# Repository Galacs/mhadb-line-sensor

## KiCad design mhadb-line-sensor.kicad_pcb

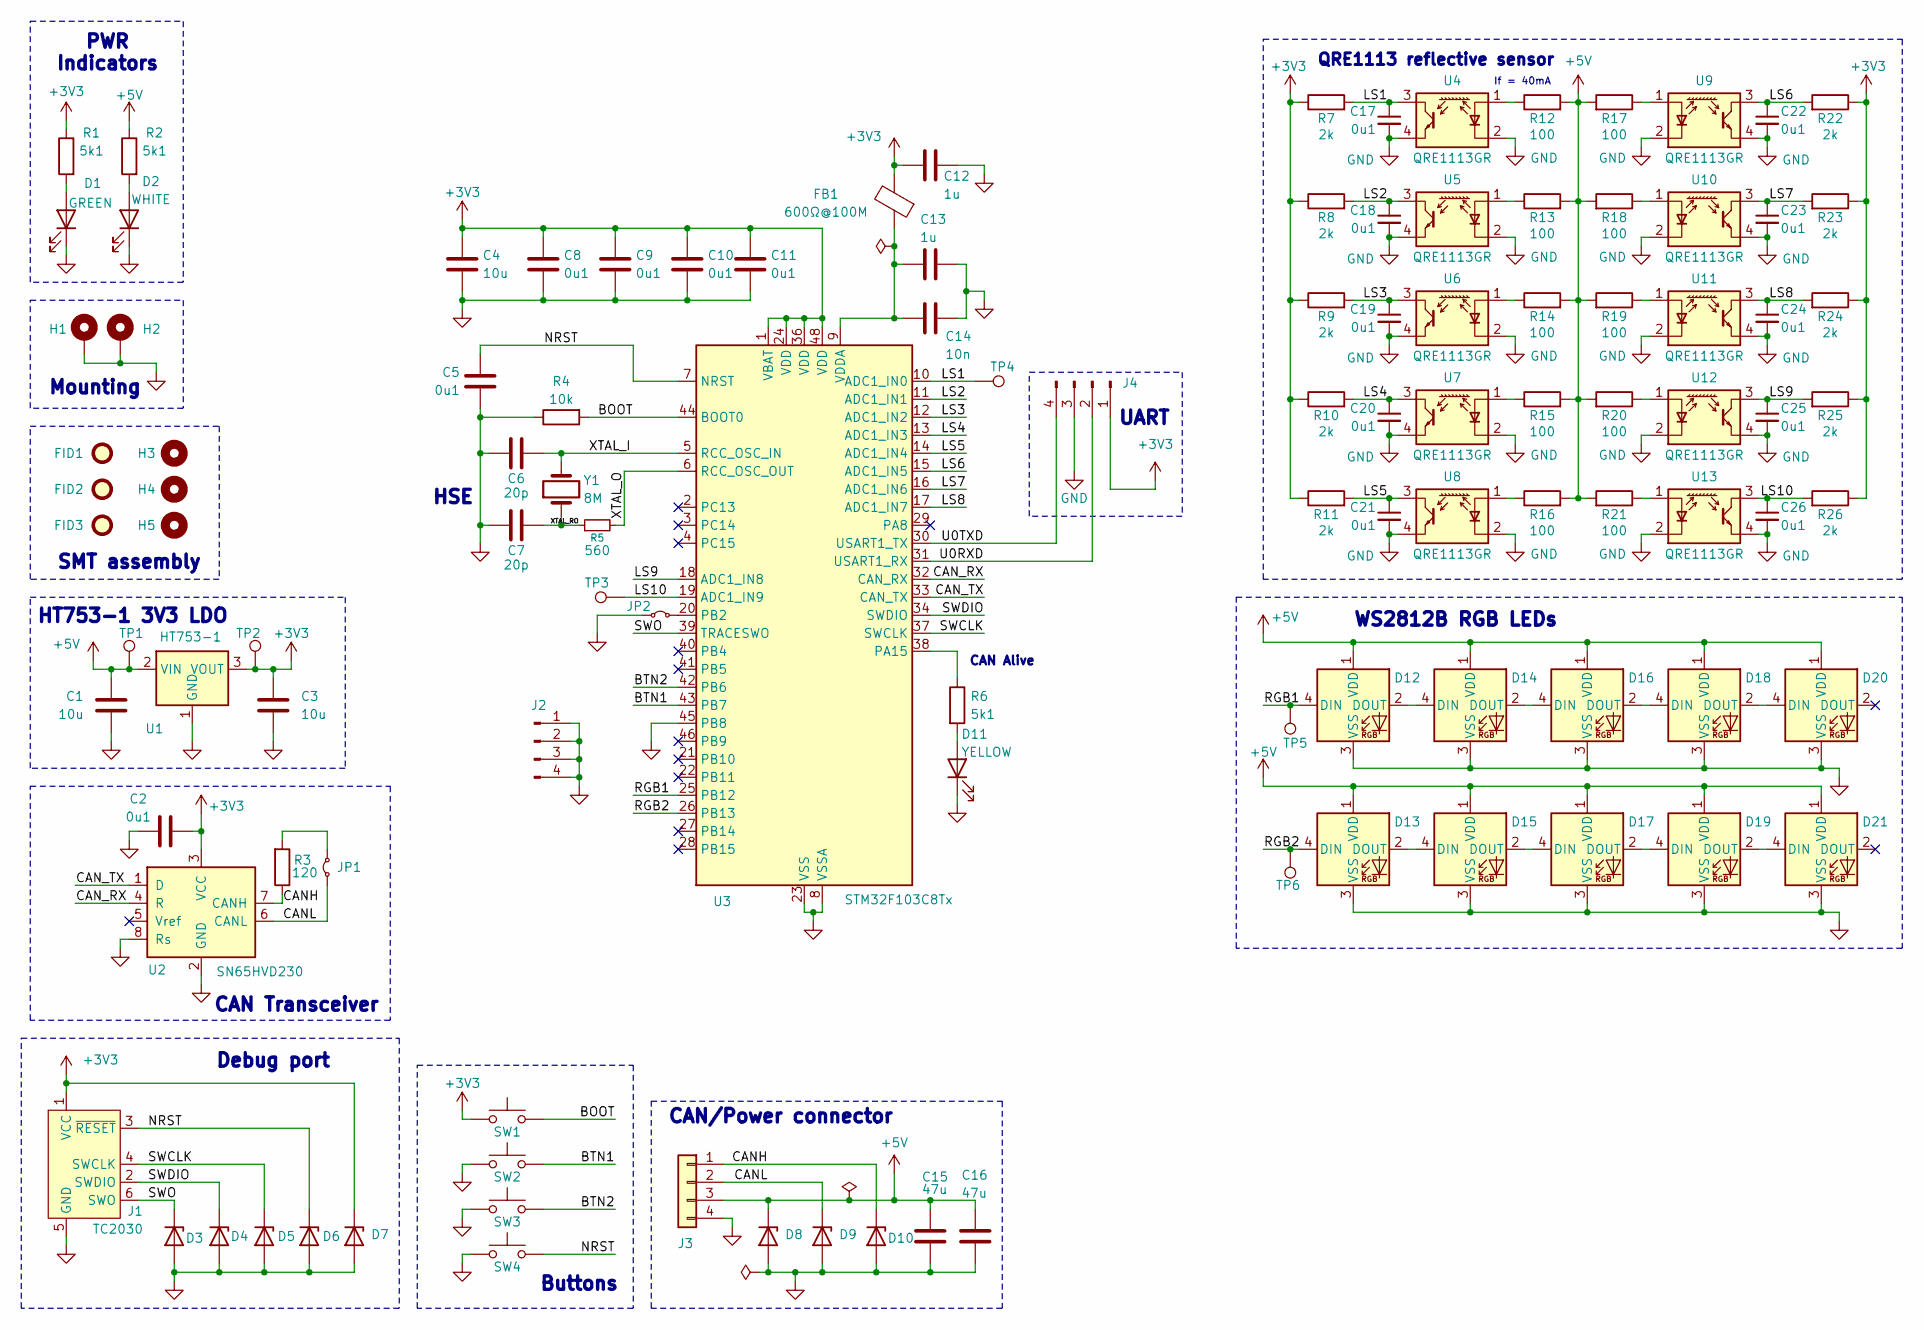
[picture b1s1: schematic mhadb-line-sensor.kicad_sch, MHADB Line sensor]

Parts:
C1, C3, C4: 10u; C_0805_2012Metric; Manufacturer Part Number GRM21BR61H106KE43L; JLCPCB Part # C440198
C2, C5, C8, C9, C10, C11, C17, C18, C19, C20, C21, C22, C23, C24, C25, C26: 0u1; C_0402_1005Metric; Manufacturer Part Number CL05B104KB54PNC; JLCPCB Part # C307331
C6, C7: 20p; C_0603_1608Metric; Manufacturer Part Number CL10C200JB8NNNC; JLCPCB Part # C1648
C12, C13: 1u; C_0402_1005Metric; Manufacturer Part Number CL05A105KA5NQNC; JLCPCB Part # C52923
C14: 10n; C_0402_1005Metric; Manufacturer Part Number CL05B103KB5NNNC; JLCPCB Part # C15195
C15, C16: 47u; C_1206_3216Metric; Manufacturer Part Number CL31A476MPHNNNE; JLCPCB Part # C96123
D1: GREEN; LED_0805_2012Metric; Manufacturer Part Number KT-0805G; JLCPCB Part # C2297
D2: WHITE; LED_0603_1608Metric; Manufacturer Part Number KT-0603W; JLCPCB Part # C2290
D3, D4, D5, D6, D7, D8, D9, D10: H5VU10U; Diode_DFN1006; Manufacturer Part Number H5VU10U; JLCPCB Part # C22395519
D11: YELLOW; LED_0805_2012Metric; Manufacturer Part Number KT-0805Y; JLCPCB Part # C2296
D12, D13, D14, D15, D16, D17, D18, D19, D20, D21: WS2812B; LED_WS2812B_PLCC4_5.0x5.0mm_P3.2mm; Manufacturer Part Number WS2812B-V5/W; JLCPCB Part # C2874885
FB1: 600Ω@100M; L_0805_2012Metric; Manufacturer Part Number MPZ2012S601ATD25; JLCPCB Part # C81034
FID1, FID2, FID3: Fiducial; Fiducial_1mm_Mask2mm
H1, H2: MountingHole_Pad; MountingHole_2.2mm_M2_Pad_Via
H3, H4, H5: MountingHole; ToolingHole_1.152mm
J1: TC2030; Tag-Connect_TC2030-IDC-NL_2x03_P1.27mm_Vertical
J2, J4: Conn_01x04_Pin; PinHeader_1x04_P2.54mm_Vertical
J3: Conn_01x04; JST_PH_S4B-PH-K_1x04_P2.00mm_Horizontal; Manufacturer Part Number S4B-PH-K-S(LF)(SN); JLCPCB Part # C157926
JP1: Jumper_2_Small_Bridged; SolderJumper-2_P1.3mm_Open_RoundedPad1.0x1.5mm
JP2: Jumper_2_Small_Bridged; SolderJumper-2_P1.3mm_Bridged_RoundedPad1.0x1.5mm
R1, R2, R6: 5k1; R_0402_1005Metric; Manufacturer Part Number 0402WGF5101TCE; JLCPCB Part # C25905
R3: 120; R_1206_3216Metric; Manufacturer Part Number 1206W4F1200T5E; JLCPCB Part # C17909
R4: 10k; R_0402_1005Metric; Manufacturer Part Number 0402WGF1002TCE; JLCPCB Part # C25744
R5: 560; R_0603_1608Metric; Manufacturer Part Number 0603WAF5600T5E; JLCPCB Part # C23204
R7, R8, R9, R10, R11, R22, R23, R24, R25, R26: 2k; R_0603_1608Metric; Manufacturer Part Number 0603WAF2201T5E; JLCPCB Part # C4190
R12, R13, R14, R15, R16, R17, R18, R19, R20, R21: 100; R_1206_3216Metric; Manufacturer Part Number 1206W4F1000T5E; JLCPCB Part # C17901
SW1, SW2, SW3, SW4: SW_Push; SW_SPST_TS-1088-xR020; Manufacturer Part Number TS-1088-AR02016; JLCPCB Part # C720477
TP1, TP2, TP3, TP4, TP5, TP6: TestPoint; TestPoint_Pad_D2.0mm
U1: HT753-1; SOT-89-3; Manufacturer Part Number HT7533-1; JLCPCB Part # C14289
U2: SN65HVD230; SOIC-8_3.9x4.9mm_P1.27mm; Manufacturer Part Number SN65HVD230DR; JLCPCB Part # C12084
U3: STM32F103C8Tx; LQFP-48_7x7mm_P0.5mm; Manufacturer Part Number STM32F103C8T6; JLCPCB Part # C8734
U4, U5, U6, U7, U8, U9, U10, U11, U12, U13: QRE1113GR; OnSemi_CASE100CY; Manufacturer Part Number QRE1113GR; JLCPCB Part # C232862
Y1: 8M; Crystal_SMD_5032-2Pin_5.0x3.2mm; Manufacturer Part Number X50328MSB2GI; JLCPCB Part # C115962

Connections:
+3V3: C2.1, C3.1, C4.1, C8.1, C9.1, C10.1, C11.1, C12.1, D7.1 (K), FB1.2, J1.1 (VCC), J4.1, R1.1, R7.1, R8.1, R9.1, R10.1, R11.1, R22.1, R23.1, R24.1, R25.1, R26.1, SW1.1, TP2.1, U1.3 (VOUT), U2.3 (VCC), U3.1 (VBAT), U3.24 (VDD), U3.36 (VDD), U3.48 (VDD)
+5V: C1.1, C15.1, C16.1, D8.1 (K), D12.1 (VDD), D13.1 (VDD), D14.1 (VDD), D15.1 (VDD), D16.1 (VDD), D17.1 (VDD), D18.1 (VDD), D19.1 (VDD), D20.1 (VDD), D21.1 (VDD), J3.3, R2.1, R12.2, R13.2, R14.2, R15.2, R16.2, R17.2, R18.2, R19.2, R20.2, R21.2, TP1.1, U1.2 (VIN)
/BOOT: R4.2, SW1.2, U3.44 (BOOT0)
/BTN1: SW2.2, U3.43 (PB7)
/BTN2: SW3.2, U3.42 (PB6)
/CANH: D10.1 (K), J3.1, R3.1, U2.7 (CANH)
/CANL: D9.1 (K), J3.2, JP1.1 (A), U2.6 (CANL)
/CAN_RX: U2.4 (R), U3.32 (CAN_RX)
/CAN_TX: U2.1 (D), U3.33 (CAN_TX)
/LS1: C17.1, R7.2, TP4.1, U3.10 (ADC1_IN0), U4.3
/LS2: C18.1, R8.2, U3.11 (ADC1_IN1), U5.3
/LS3: C19.1, R9.2, U3.12 (ADC1_IN2), U6.3
/LS4: C20.1, R10.2, U3.13 (ADC1_IN3), U7.3
/LS5: C21.1, R11.2, U3.14 (ADC1_IN4), U8.3
/LS6: C22.1, R22.2, U3.15 (ADC1_IN5), U9.3
/LS7: C23.1, R23.2, U3.16 (ADC1_IN6), U10.3
/LS8: C24.1, R24.2, U3.17 (ADC1_IN7), U11.3
/LS9: C25.1, R25.2, U3.18 (ADC1_IN8), U12.3
/LS10: C26.1, R26.2, TP3.1, U3.19 (ADC1_IN9), U13.3
/NRST: C5.1, D6.1 (K), J1.3 (~RESET), SW4.2, U3.7 (NRST)
/RGB1: D12.4 (DIN), TP5.1, U3.25 (PB12)
/RGB2: D13.4 (DIN), TP6.1, U3.26 (PB13)
/SWCLK: D5.1 (K), J1.4 (SWCLK), U3.37 (SWCLK)
/SWDIO: D4.1 (K), J1.2 (SWDIO), U3.34 (SWDIO)
/SWO: D3.1 (K), J1.6 (SWO), U3.39 (TRACESWO)
/U0RXD: J4.2, U3.31 (USART1_RX)
/U0TXD: J4.4, U3.30 (USART1_TX)
/XTAL_I: C6.1, U3.5 (RCC_OSC_IN), Y1.2
/XTAL_O: R5.2, U3.6 (RCC_OSC_OUT)
/XTAL_RO: C7.1, R5.1, Y1.1
GND: C1.2, C2.2, C3.2, C4.2, C5.2, C6.2, C7.2, C8.2, C9.2, C10.2, C11.2, C12.2, C13.2, C14.2, C15.2, C16.2, C17.2, C18.2, C19.2, C20.2, C21.2, C22.2, C23.2, C24.2, C25.2, C26.2, D1.1 (K), D2.1 (K), D3.2 (A), D4.2 (A), D5.2 (A), D6.2 (A), D7.2 (A), D8.2 (A), D9.2 (A), D10.2 (A), D11.1 (K), D12.3 (VSS), D13.3 (VSS), D14.3 (VSS), D15.3 (VSS), D16.3 (VSS), D17.3 (VSS), D18.3 (VSS), D19.3 (VSS), D20.3 (VSS), D21.3 (VSS), H1.1, H2.1, J1.5 (GND), J2.1, J2.2, J2.3, J2.4, J3.4, J4.3, JP2.1 (A), R4.1, SW2.1, SW3.1, SW4.1, U1.1 (GND), U2.2 (GND), U2.8 (Rs), U3.8 (VSSA), U3.23 (VSS), U3.35 (VSS), U3.45 (PB8), U3.47 (VSS), U4.2 (K), U4.4, U5.2 (K), U5.4, U6.2 (K), U6.4, U7.2 (K), U7.4, U8.2 (K), U8.4, U9.2 (K), U9.4, U10.2 (K), U10.4, U11.2 (K), U11.4, U12.2 (K), U12.4, U13.2 (K), U13.4
unnamed: D1.2 (A), R1.2
unnamed: D2.2 (A), R2.2
unnamed: D11.2 (A), R6.2
unnamed: D12.2 (DOUT), D14.4 (DIN)
unnamed: D13.2 (DOUT), D15.4 (DIN)
unnamed: D14.2 (DOUT), D16.4 (DIN)
unnamed: D15.2 (DOUT), D17.4 (DIN)
unnamed: D16.2 (DOUT), D18.4 (DIN)
unnamed: D17.2 (DOUT), D19.4 (DIN)
unnamed: D18.2 (DOUT), D20.4 (DIN)
unnamed: D19.2 (DOUT), D21.4 (DIN)
unnamed: JP1.2 (B), R3.2
unnamed: JP2.2 (B), U3.20 (PB2)
unnamed: R6.1, U3.38 (PA15)
unnamed: C13.1, C14.1, FB1.1, U3.9 (VDDA)
unnamed: R12.1, U4.1 (A)
unnamed: R13.1, U5.1 (A)
unnamed: R14.1, U6.1 (A)
unnamed: R15.1, U7.1 (A)
unnamed: R16.1, U8.1 (A)
unnamed: R17.1, U9.1 (A)
unnamed: R18.1, U10.1 (A)
unnamed: R19.1, U11.1 (A)
unnamed: R20.1, U12.1 (A)
unnamed: R21.1, U13.1 (A)

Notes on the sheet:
CAN Transceiver
WS2812B RGB LEDs
Buttons
CAN Alive
If = 40mA
UART
PWR Indicators
SMT assembly
QRE1113 reflective sensor
Mounting
HT753-1 3V3 LDO
Debug port
CAN/Power connector
HSE

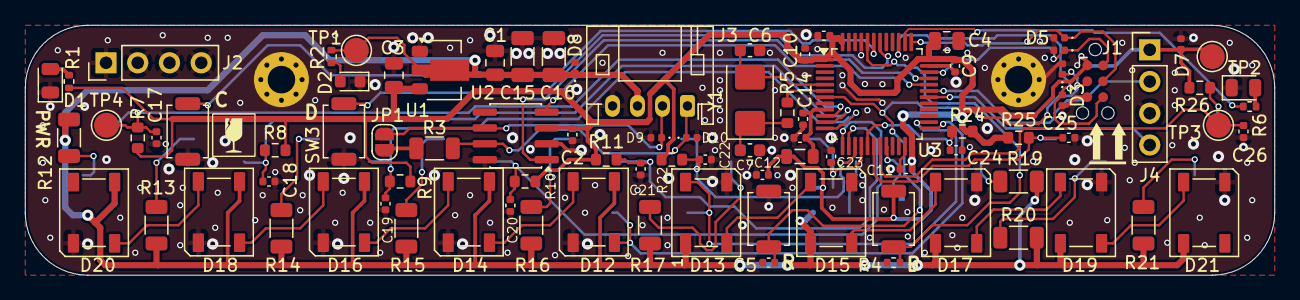
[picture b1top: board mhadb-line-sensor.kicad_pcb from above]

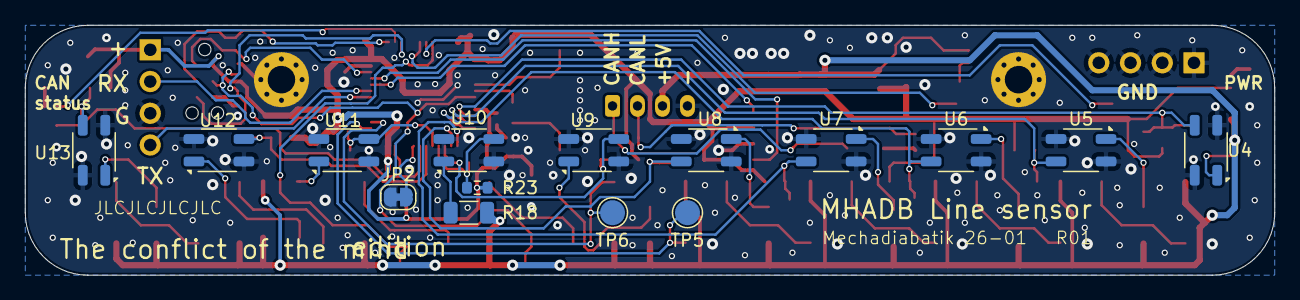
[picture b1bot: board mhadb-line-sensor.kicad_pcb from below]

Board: 2 copper layers, 100.0 x 20.0 mm, 106 parts (15 on the bottom side), 56 nets.

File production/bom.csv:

Designator,Footprint,Quantity,Value,LCSC Part #
"C1, C3, C4",0805,3,10u,C440198
"C10, C11, C17, C18, C19, C2, C20, C21, C22, C23, C24, C25, C26, C5, C8, C9",0402,16,0u1,C307331
"C12, C13",0402,2,1u,C52923
C14,0402,1,10n,C15195
"C15, C16",1206,2,47u,C96123
"C6, C7",0603,2,20p,C1648
D1,0805,1,GREEN,C2297
"D10, D3, D4, D5, D6, D7, D8, D9",Diode_DFN1006,8,H5VU10U,C22395519
D11,0805,1,YELLOW,C2296
"D12, D13, D14, D15, D16, D17, D18, D19, D20, D21",LED_WS2812B_PLCC4_5.0x5.0mm_P3.2mm,10,WS2812B,C2874885
D2,0603,1,WHITE,C2290
FB1,0805,1,600Ω@100M,C1015
J3,JST_PH_S4B-PH-K_1x04_P2.00mm_Horizontal,1,Conn_01x04,C157926
"R1, R2, R6",0402,3,5k1,C25905
"R10, R11, R22, R23, R24, R25, R26, R7, R8, R9",0603,10,2k,C4190
"R12, R13, R14, R15, R16, R17, R18, R19, R20, R21",1206,10,100,C17901
R3,1206,1,120,C17909
R4,0402,1,10k,C25744
R5,0603,1,560,C23204
"SW1, SW2, SW3, SW4",SW_SPST_TS-1088-xR020,4,SW_Push,C720477
U1,SOT-89-3,1,HT753-1,C14289
"U10, U11, U12, U13, U4, U5, U6, U7, U8, U9",OnSemi_CASE100CY,10,QRE1113GR,C232862
U2,SOIC-8_3.9x4.9mm_P1.27mm,1,SN65HVD230,C12084
U3,LQFP-48_7x7mm_P0.5mm,1,STM32F103C8Tx,C8734
Y1,Crystal_SMD_5032-2Pin_5.0x3.2mm,1,8M,C115962

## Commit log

2026-01-08 schem: add STM32F103C8Tx MCU with decoupling
2026-01-08 schem: import HSE and boot/rst
2026-01-08 schem: add CAN/Power connector
2026-01-08 schem: add TC2030 SWD debug port
2026-01-08 schem: add SN65HVD230 CAN transceiver
2026-01-08 schem: add UART1 header
2026-01-08 schem: add 10x QRE1113 reflective sensor
2026-01-08 schem: add 10x WS2812B RGB LEDs
2026-01-09 schem: add BOOT and RST btns
2026-01-09 schem: add 3v3 input bulk capacitance
2026-01-09 schem: add indicator leds
2026-01-09 schem: add general btns
2026-01-09 schem: connect RGB leds to MCU
2026-01-09 schem: add spare GPIOs
2026-01-09 schem: switch to 5v architecture and add 3v3 LDO
2026-01-09 schem: add no connects
2026-01-09 schem: add test points
2026-01-09 schem: run and fix ERC
2026-01-09 schem: add assembly and mounting holes
2026-01-09 schem: add net classes
2026-01-09 schem: add missing footprints and ordering info
2026-01-09 schem: add title
2026-01-09 schem: renumber
2026-01-09 pcb: create file and import stackup and constraints
2026-01-09 pcb: import footprints from schema
2026-01-09 schem/pcb: add EM stop btn
2026-01-09 pcb: add board outline
2026-01-09 pcb: initial sensor placement
2026-01-09 pcb: initial rough layout
2026-01-09 pcb: add gnd planes
2026-01-09 pcb: add gnd vias
2026-01-09 pcb: add SWD routing
2026-01-09 pcb: add CAN routing
2026-01-09 pcb: add UART routing
2026-01-09 pcb: add QRE1113 collectors routing
2026-01-09 pcb: add RGB leds routing
2026-01-10 schem/pcb: add BOOT1 strapping
2026-01-10 pcb: add QRE1113 emitters routing
2026-01-10 pcb: add 3v3 routing
2026-01-10 pcb: add 5v routing
2026-01-10 pcb: add BOOT and RST routing
2026-01-10 pcb: add tag connect RST and CAN status led routing
2026-01-10 pcb: add btns routing
2026-01-10 schem/pcb: remove spare GPIOs
2026-01-10 pcb: add stitching vias
2026-01-10 pcb: run and fix DRC
2026-01-10 pcb(silkscreen): clean reference designators
2026-01-10 pcb: add title
2026-01-10 pcb(silkscreen): add user txt
2026-01-10 pcb(silkscreen): replace 何何何何 placeholder
2026-01-10 add production files
2026-01-11 pcb(silkscreen): add icons
2026-01-11 regenerate production files
2026-01-11 update BOM
